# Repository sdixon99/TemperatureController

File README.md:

TemperatureController
=====================

Arduino compatible PID based temperature controller.

This controller has been used to control both hot plates and toaster ovens for reflow soldering.  It has also been used for a few other tasks involving temperature control.

The sensor most often used is a modified Harbor Freight IR thermometer which works well for sensing the temperature of a hot plate surface.  The design includes an optional K type thermocouple interface which is more suitable for temperature sensing in a toaster oven (and liquids, etc).

The original design used a MAX6675 thermocouple interface chip.  The code for that design is checked in under tag v1_2.  However, this chip is now end-of-life and has been replaced by the MAX31855.  The latest software and hardware files support the MAX31855.  The MAX31855 is a 3.3V chip so the V1.5 design incorporates 5V to 3.3V level shifting using the pull-ups and diodes design from the Adafruit [breakout board](http://adafruit.com/products/269).

For more information on the earlier design and some additional construction details, see my [blog](http://dorkbotpdx.org/blog/scott_d/installing_the_temperature_controller_code) and the additional information linked there.

The firmware is derived from the [Bare Bones Coffee Controller](http://playground.arduino.cc/Main/BarebonesPIDForEspresso), some standard Arduino libraries and a couple of non-standard libraries (which are included in the libs subdirectory).  

[Pete Skeggs](https://github.com/plskeggs) has modified the firmware to more carefully control the PID timing loop and has gotten good results with a toaster oven.  Note that his code is for the V1.2 board (MAX6675).  It shouldn't be hard to update to the V1.5 design based on the MAX31855.

Non-standard Arduino libraries used (snapshots in libs subdirectory):

RotaryEncoder, written by SunboX: [http://www.arduino.cc/cgi-bin/yabb2/YaBB.pl?num=1205879808]().  The version in libs is updated for Arduino 1.0.

max6675 by Ryan McLaughlin: [http://code.google.com/p/max6675-arduino-library]())

max31855, by Ryan McLuahghlin: [http://ryanjmclaughlin.com/wiki/MAX31855_Arduino_Library]()

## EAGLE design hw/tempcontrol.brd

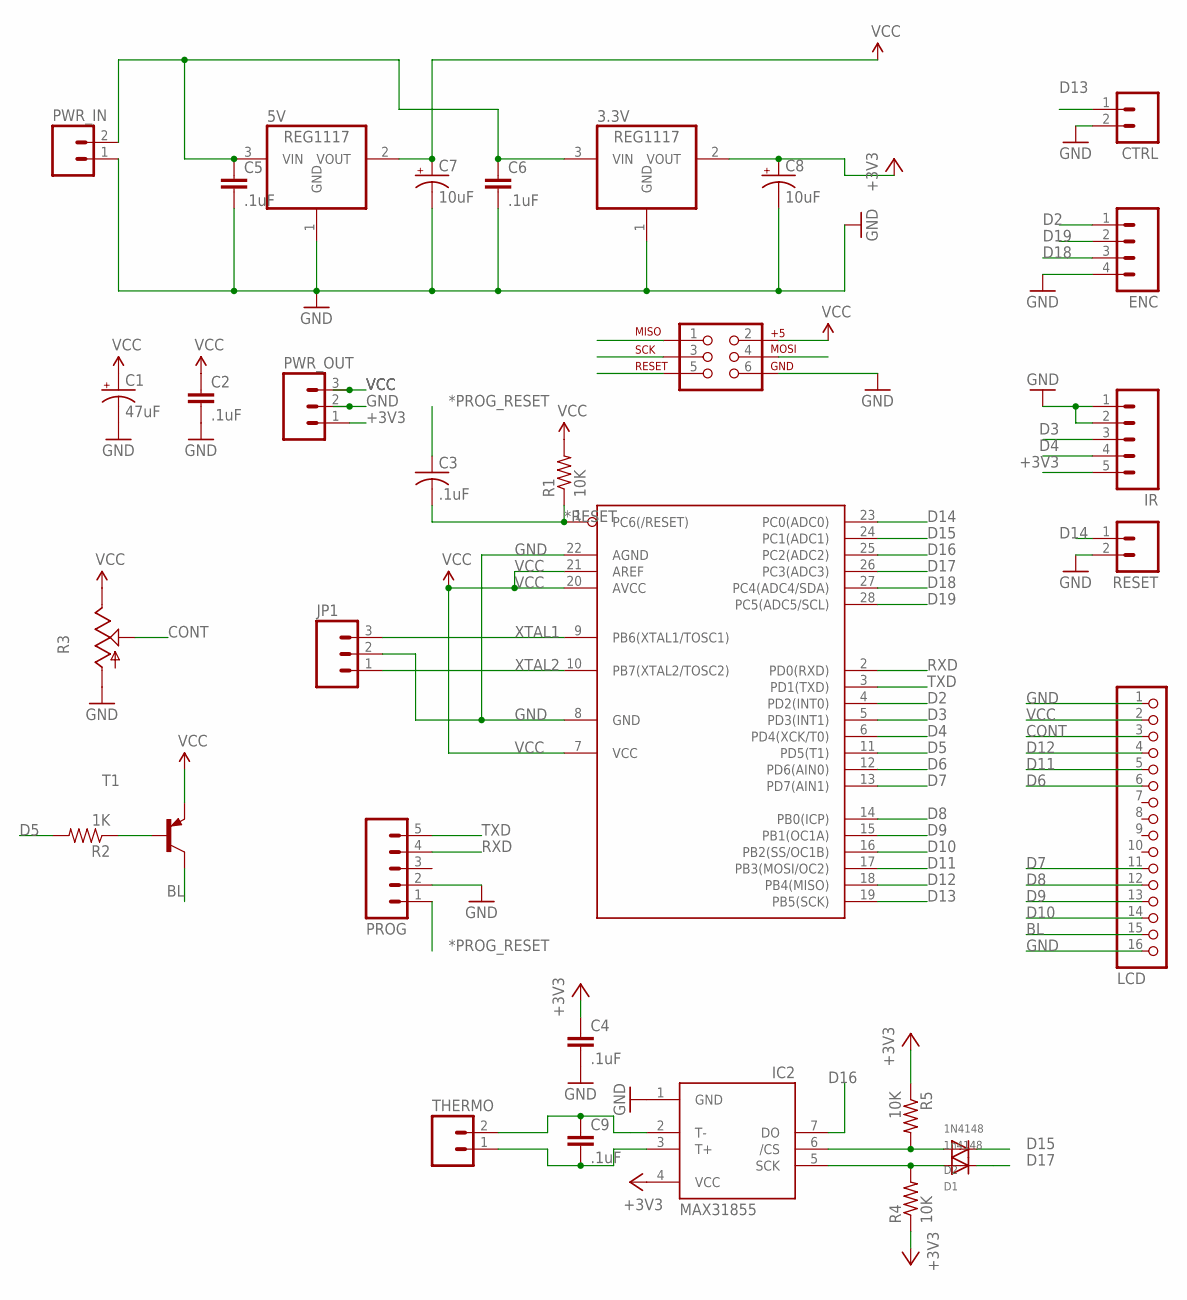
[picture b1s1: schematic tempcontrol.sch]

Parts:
3.3V, 5V: REG1117; SOT223
C1: 47uF; CPOL-RADIAL-10UF-25V
C2, C4, C5, C6, C9: .1uF; 0805
C3: .1uF; C0805
C7, C8: 10uF; EIA3528
CTRL: M02LOCK; 1X02_LOCK
D1: 1n4148; SOD-323F
D2: 1N4148; SOD-323F
ENC: M04LOCK; 1X04_LOCK
IC1: MEGA8-P; DIL28-3
IC2: MAX31855; SO08
IR: M05LOCK; 1X05_LOCK
JP1: M03LOCK; 1X03_LOCK
JP7: LCD; 1X16
PROG: PROG; 1X05_LOCK
PWR_IN: M02LOCK; 1X02_LOCK
PWR_OUT: M03LOCK; 1X03_LOCK
R1: 10K; 0805
R2: 1K; 0805
R3: TRIM_US-B64Y; B64Y
R4, R5: 10K; R0805
RESET: M02LOCK; 1X02_LOCK
T1: 2N3906-PNP-TO92-EBC; TO92-EBC
THERMO: M02LOCK; 1X02_LOCK
U$1: AVR_SPI_PRG_6NS; 2X3-NS

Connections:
*PROG_RESET: C3.1, PROG.1
*RESET: C3.2, IC1.1 (PC6(/RESET)), R1.1, U$1.5
+3V3: 3.3V.2 (VOUT), C4.1, C8.A (+), IC2.4 (VCC), IR.5, PWR_OUT.1, R4.1, R5.1
BL: JP7.15, T1.C
CONT: JP7.3, R3.S
CS: D2.A, IC2.6 (/CS), R5.2
D2: ENC.1, IC1.4 (PD2(INT0))
D3: IC1.5 (PD3(INT1)), IR.3
D4: IC1.6 (PD4(XCK/T0)), IR.4
D5: IC1.11 (PD5(T1)), R2.2
D6: IC1.12 (PD6(AIN0)), JP7.6
D7: IC1.13 (PD7(AIN1)), JP7.11
D8: IC1.14 (PB0(ICP)), JP7.12
D9: IC1.15 (PB1(OC1A)), JP7.13
D10: IC1.16 (PB2(SS/OC1B)), JP7.14
D11: IC1.17 (PB3(MOSI/OC2)), JP7.5, U$1.4
D12: IC1.18 (PB4(MISO)), JP7.4, U$1.1
D13: CTRL.1, IC1.19 (PB5(SCK)), U$1.3
D14: IC1.23 (PC0(ADC0)), RESET.1
D15: D2.C, IC1.24 (PC1(ADC1))
D16: IC1.25 (PC2(ADC2)), IC2.7 (DO)
D17: D1.C, IC1.26 (PC3(ADC3))
D18: ENC.3, IC1.27 (PC4(ADC4/SDA))
D19: ENC.2, IC1.28 (PC5(ADC5/SCL))
GND: 3.3V.1 (GND), 5V.1 (GND), C1.2 (-), C2.2, C4.2, C5.2, C6.2, C7.C (-), C8.C (-), CTRL.2, ENC.4, IC1.8 (GND), IC1.22 (AGND), IC2.1 (GND), IR.1, IR.2, JP1.2, JP7.1, JP7.16, PROG.2, PWR_IN.1, PWR_OUT.2, R3.A, RESET.2, U$1.6
unnamed: R2.1, T1.B
POS_IN: 3.3V.3 (VIN), 5V.3 (VIN), C5.1, C6.1, PWR_IN.2
RXD: IC1.2 (PD0(RXD)), PROG.4
SCK: D1.A, IC2.5 (SCK), R4.2
T+: C9.2, IC2.3 (T+), THERMO.1
T-: C9.1, IC2.2 (T-), THERMO.2
TXD: IC1.3 (PD1(TXD)), PROG.5
VCC: 5V.2 (VOUT), C1.1 (+), C2.1, C7.A (+), IC1.7 (VCC), IC1.20 (AVCC), IC1.21 (AREF), JP7.2, PWR_OUT.3, R1.2, R3.E, T1.E, U$1.2
XTAL1: IC1.9 (PB6(XTAL1/TOSC1)), JP1.3
XTAL2: IC1.10 (PB7(XTAL2/TOSC2)), JP1.1

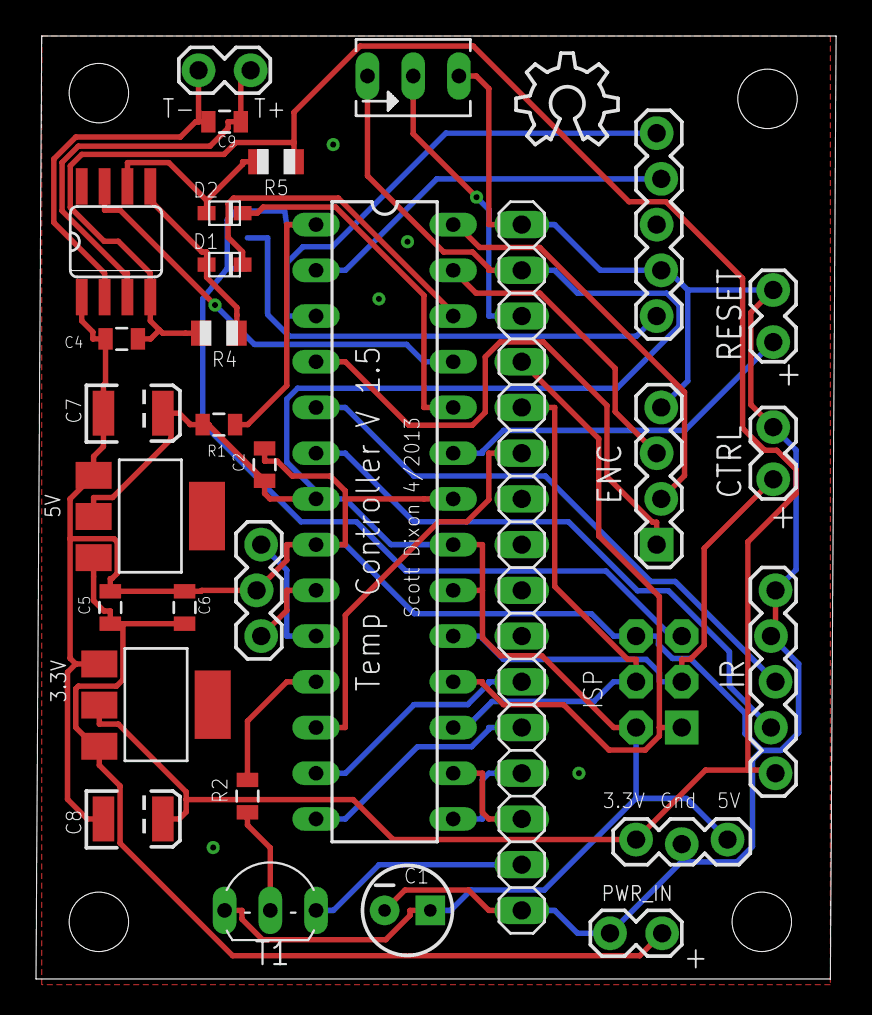
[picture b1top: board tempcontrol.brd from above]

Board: 2 copper layers, 44.5 x 52.4 mm, 37 parts (1 on the bottom side), 35 nets.

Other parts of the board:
U$2: OSHW_8X200_NOTEXT
U$3, U$4, U$5, U$6: STAND-OFF

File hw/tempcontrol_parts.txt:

Part    Value     Device              Package              Description

3.3V    REG1117   LD1117              SOT223               800mA and 1A Low Dropout (LDO) Digikey 497-1241-1-ND
5V      REG1117   LD1117              SOT223               800mA and 1A Low Dropout (LDO) Digikey 497-1243-1-ND
C5      .1uF      CAP0805             0805                 Capacitor
C6      .1uF      CAP0805             0805                 Capacitor
C7      10uF      CAP_POL3528         EIA3528              Tantalum Capacitor Polarized Digikey 718-1124-1-ND
C8      10uF      CAP_POL3528         EIA3528              Tantalum Capacitor Polarized Digikey 718-1124-1-ND

C1      10uF      CAP_POLPTH2         CPOL-RADIAL-10UF-25V Capacitor Polarized   Digikey P813-ND                       
C2      .1uF      CAP0805             0805                 Capacitor
C3      .1uF      CAP0603             0603
R1      10K       RESISTOR            0805                 Resistor
R2      1K        RESISTOR            0805                 Resistor
R3      10K       TRIM_US-B64Y        B64Y                 POTENTIOMETER Digikey 3352T-103LF-ND
IC1     MEG3288-P MEGA328-P           DIL28-3 MICROCONTROLLER + 28 pin socket  
T1                2N3906-PNP-TO92-EBC TO92-EBC             PNP Transistor
JP1               16MHz Resonator     1X03_LOCK            Digkikey X908-ND

IR                M05LOCK             1X05_LOCK            Header 5 pin
JP7     LCD       PINHD-1X16          1X16                 Female Pin Header
CTRL              M02LOCK             1X02_LOCK            Header 2 pin
ENC               M04LOCK             1X04_LOCK            Header 4 pin                                     
PROG    PROG      M05LOCK             1X05_LOCK            Header 5 pin
PWR_IN            M02LOCK             1X02_LOCK            Header 2 pin
PWR_OUT           M03LOCK             1X03_LOCK            Header 3 pin
RESET             M02LOCK             1X02_LOCK            Header 2 pin
U$1               AVR_SPI_PRG_6NS     2X3-NS               AVR ISP 6 Pin

Encoder (like Bourns 652-PEC11-4215F-S2411R-4215F-S0024) or switches to
change settings

16x2 LCD using HD44780 compatible controller

Harbor Freight IR Thermometer (either Item #93984 or Item #93983)

Optional parts for Thermocouple interface
C4      .1uF      CAP0805             0805                 Capacitor
U$2     MAX31855  MAX31855KASA+       SO08                 Digkikey 700-MAX31855KASA+
D1      1N4148    DIODE               SOD-323F             Mouser 78-1N4148WS-V
D2      1N4148    DIODE               SOD-323F             Mouser 78-1N4148WS-V
R4      10K       RESISTOR            0805                 Resistor
R5      10K       RESISTOR            0805                 Resistor

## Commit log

2013-05-13 Initial checkin of code for V1.2 hardware which uses the MAX6675 thermocouple interface chip. New designs use the MAX31855 since the MAX6675 is end-of-life status from Maxim.
2013-05-13 Firmware and hardware for the v1.5 version which uses the MAX31855 thermocouple interface chip.
